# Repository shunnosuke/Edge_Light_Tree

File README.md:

# PCB for Edge Light Tree

## License

This work is licensed under a [Creative Commons Attribution 4.0 International License](http://creativecommons.org/licenses/by/4.0/).

---
&#169; 2019 Shunnosuke Tokuhira

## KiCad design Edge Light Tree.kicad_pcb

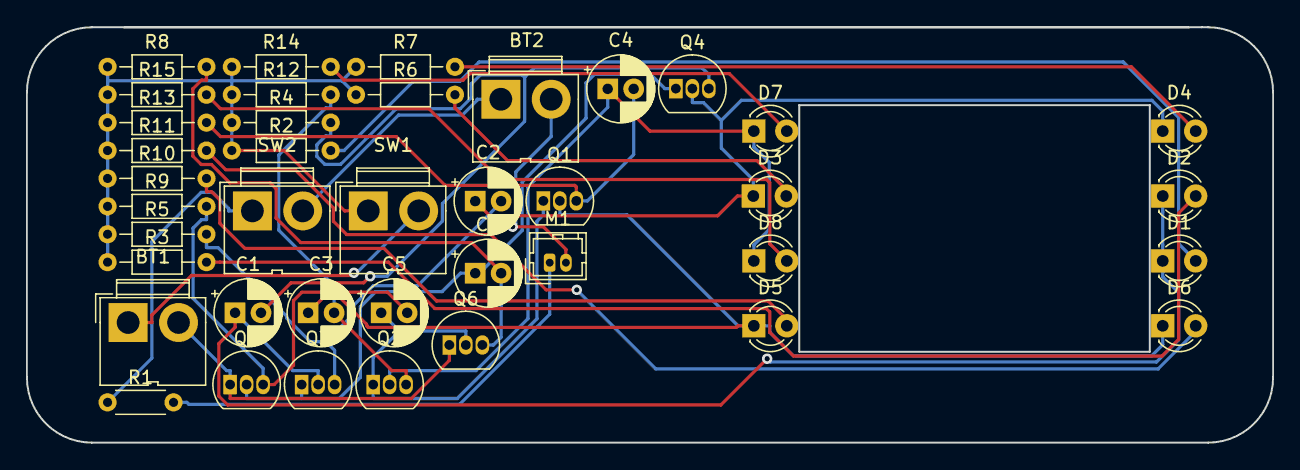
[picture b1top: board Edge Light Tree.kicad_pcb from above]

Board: 2 copper layers, 96.0 x 32.0 mm, 40 parts (0 on the bottom side), 27 nets.

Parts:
BT1, BT2: Battery_Cell; JWT_A3963_1x02_P3.96mm_Vertical
C1, C2, C3, C4, C5, C6: CP; CP_Radial_D5.0mm_P2.00mm
D1, D2, D3, D4, D5, D6, D7, D8: LED; LED_D3.0mm_Clear
M1: Motor_DC; Hirose_DF13-02P-1.25DSA_1x02_P1.25mm_Vertical
Q1, Q2, Q3, Q4, Q5, Q6: 2SC1815; TO-92_Inline
R1: R; R_Axial_DIN0204_L3.6mm_D1.6mm_P5.08mm_Horizontal
R2, R3, R4, R5, R6, R7, R8, R9, R10, R11, R12, R13, R14, R15: R; R_Axial_DIN0204_L3.6mm_D1.6mm_P7.62mm_Horizontal
SW1, SW2: SW_DIP_x01; JWT_A3963_1x02_P3.96mm_Vertical

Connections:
unnamed: BT1.1, SW1.2
unnamed: BT1.2, Q5.1, Q6.1
unnamed: BT2.1, SW2.2
unnamed: BT2.2, M1.2
unnamed: C1.1, D1.1, D2.1, Q3.2
unnamed: C1.2, Q4.3, R4.2
unnamed: C2.1, D3.1, D4.1, Q4.2
unnamed: C2.2, Q3.3, R5.2
unnamed: C3.1, D5.1, D6.1, Q1.2
unnamed: C3.2, Q2.3, R12.2
unnamed: C4.1, D7.1, D8.1, Q2.2
unnamed: C4.2, Q1.3, R13.2
unnamed: C5.1, Q1.1, Q2.1, Q6.2
unnamed: C5.2, Q5.3, R9.2
unnamed: C6.1, Q3.1, Q4.1, Q5.2
unnamed: C6.2, Q6.3, R8.2
unnamed: D1.2, R2.2
unnamed: D2.2, R3.2
unnamed: D3.2, R6.2
unnamed: D4.2, R7.2
unnamed: D5.2, R10.2
unnamed: D6.2, R11.2
unnamed: D7.2, R14.2
unnamed: D8.2, R15.2
unnamed: M1.1, R1.2
unnamed: R1.1, SW2.1
unnamed: R2.1, R3.1, R4.1, R5.1, R6.1, R7.1, R8.1, R9.1, R10.1, R11.1, R12.1, R13.1, R14.1, R15.1, SW1.1

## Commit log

2019-02-17 Shunnosuke's design on tokuhira's PC
2019-02-17 Board mounting holes until installation
2019-07-15 ほぼ完成版
2019-10-02 ドリルファイルを追加
2019-10-03 ドリルファイル
